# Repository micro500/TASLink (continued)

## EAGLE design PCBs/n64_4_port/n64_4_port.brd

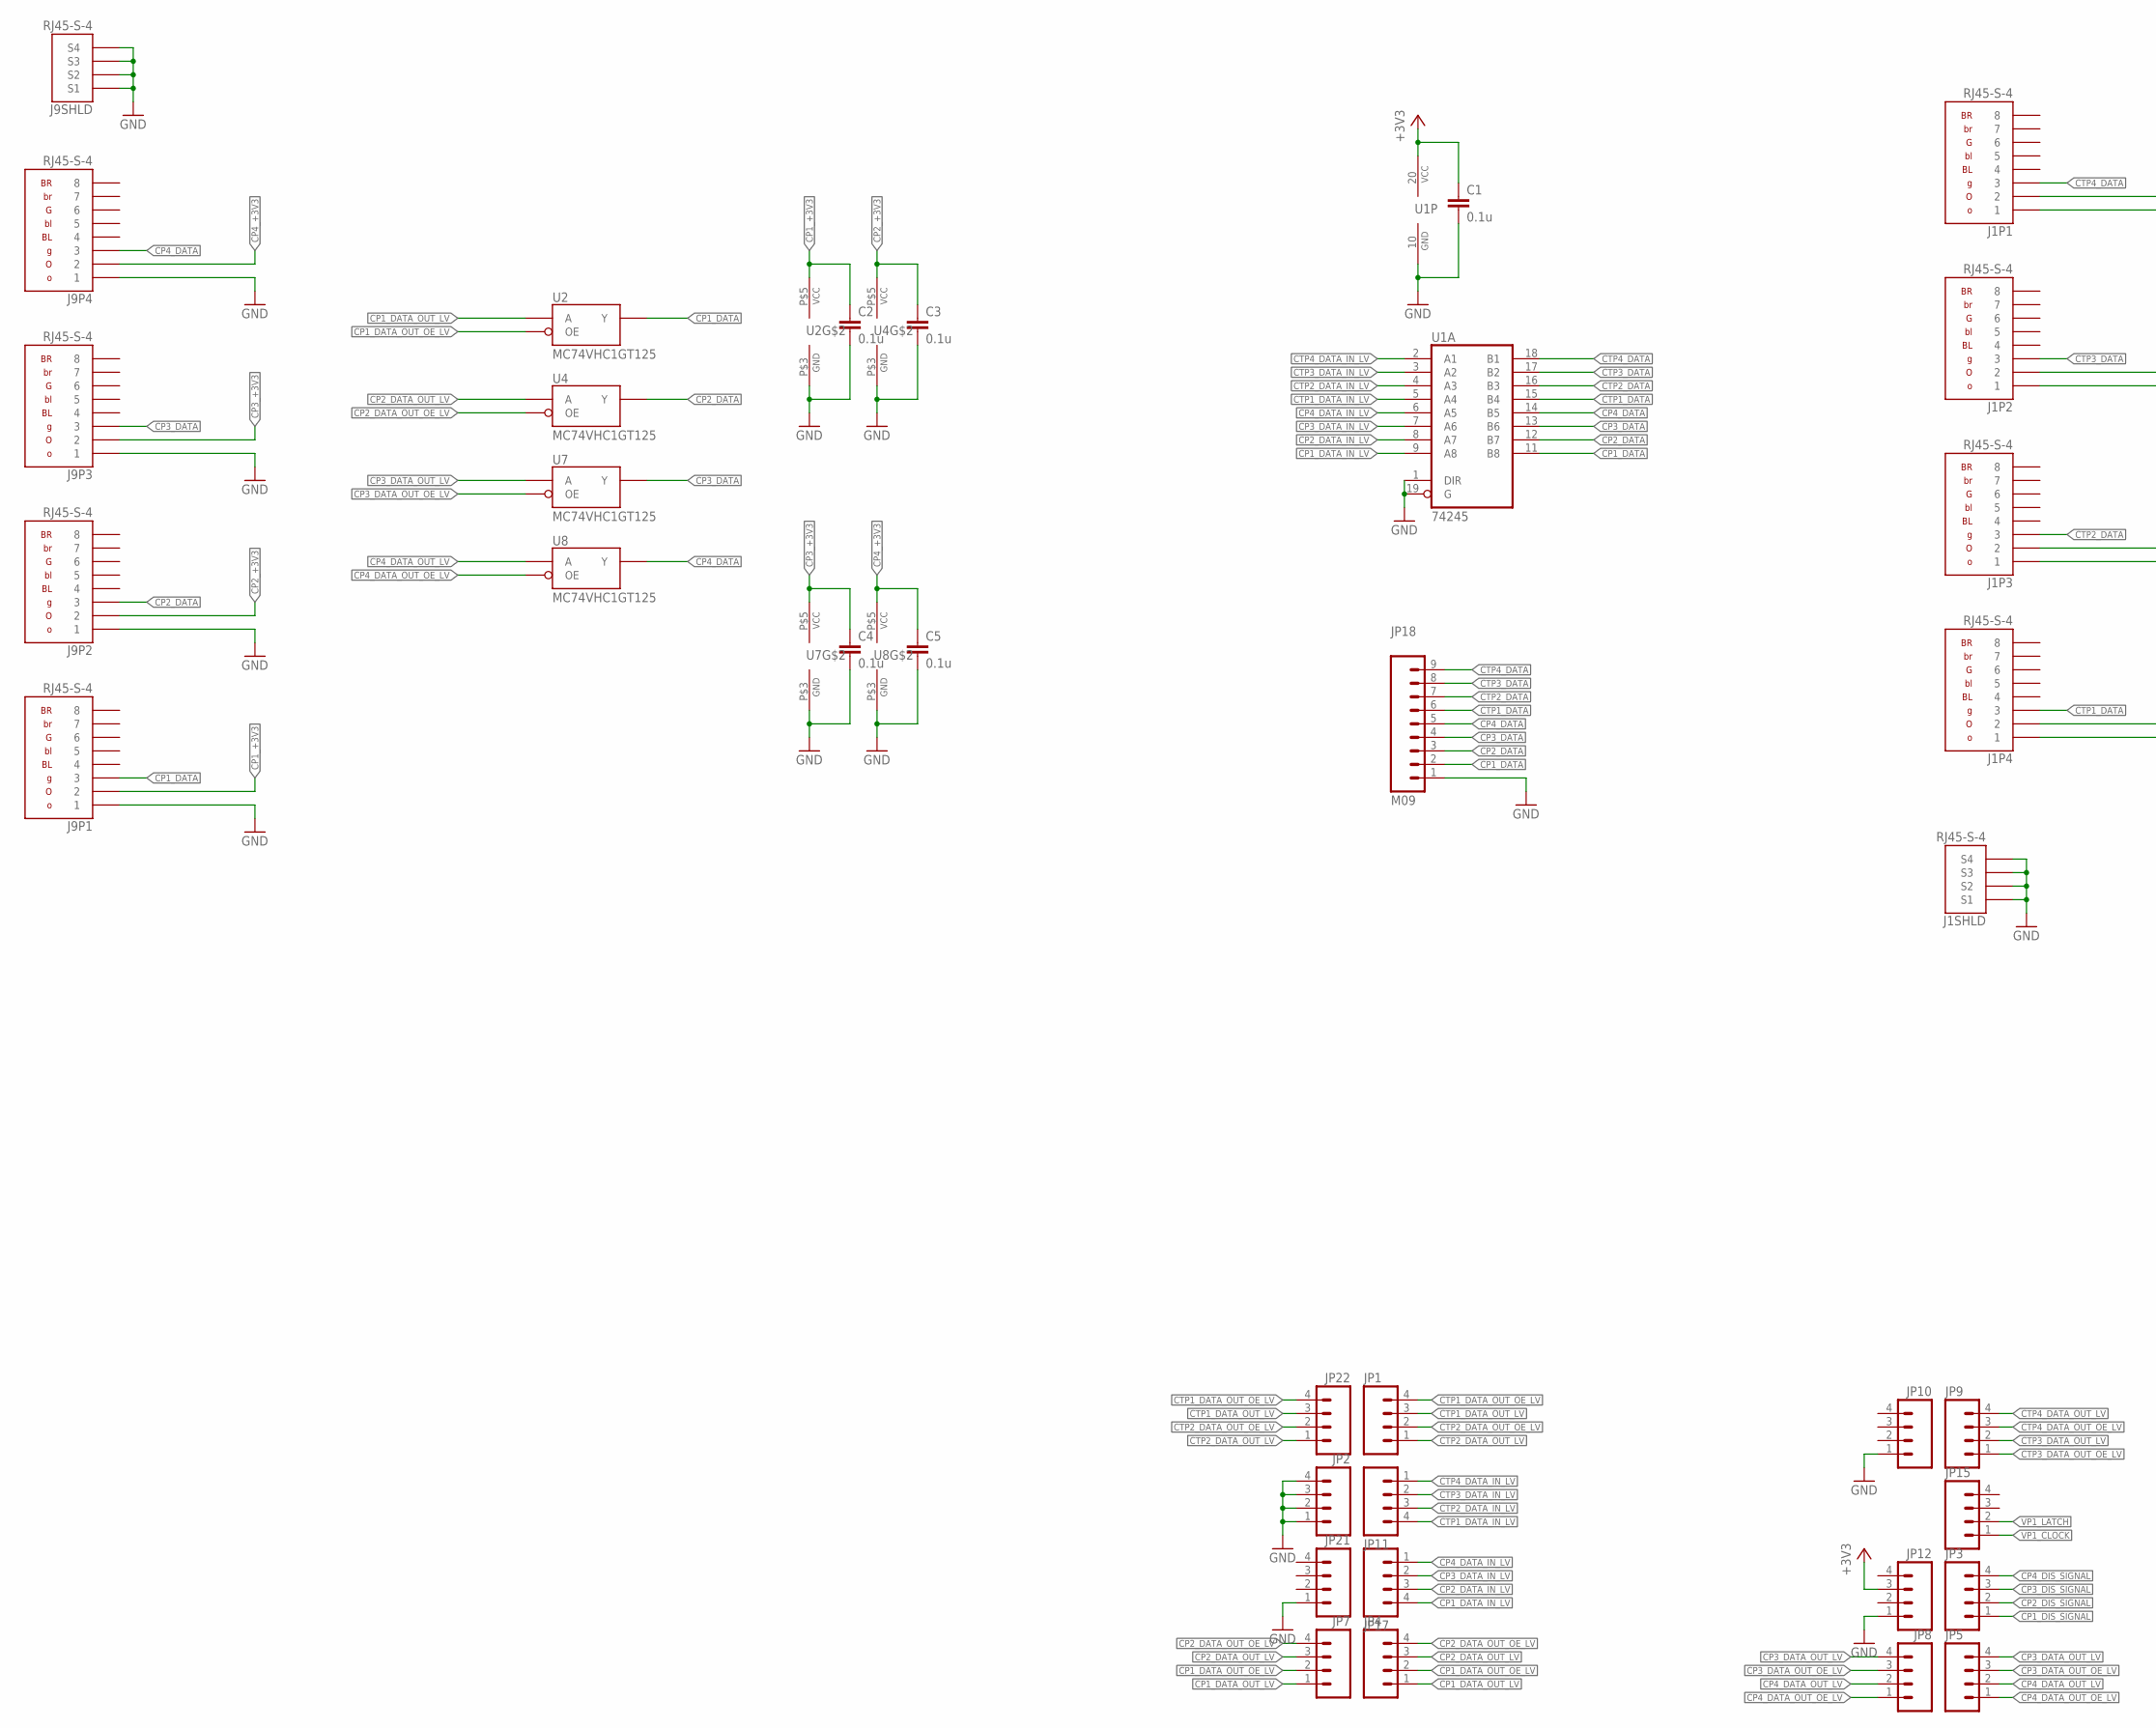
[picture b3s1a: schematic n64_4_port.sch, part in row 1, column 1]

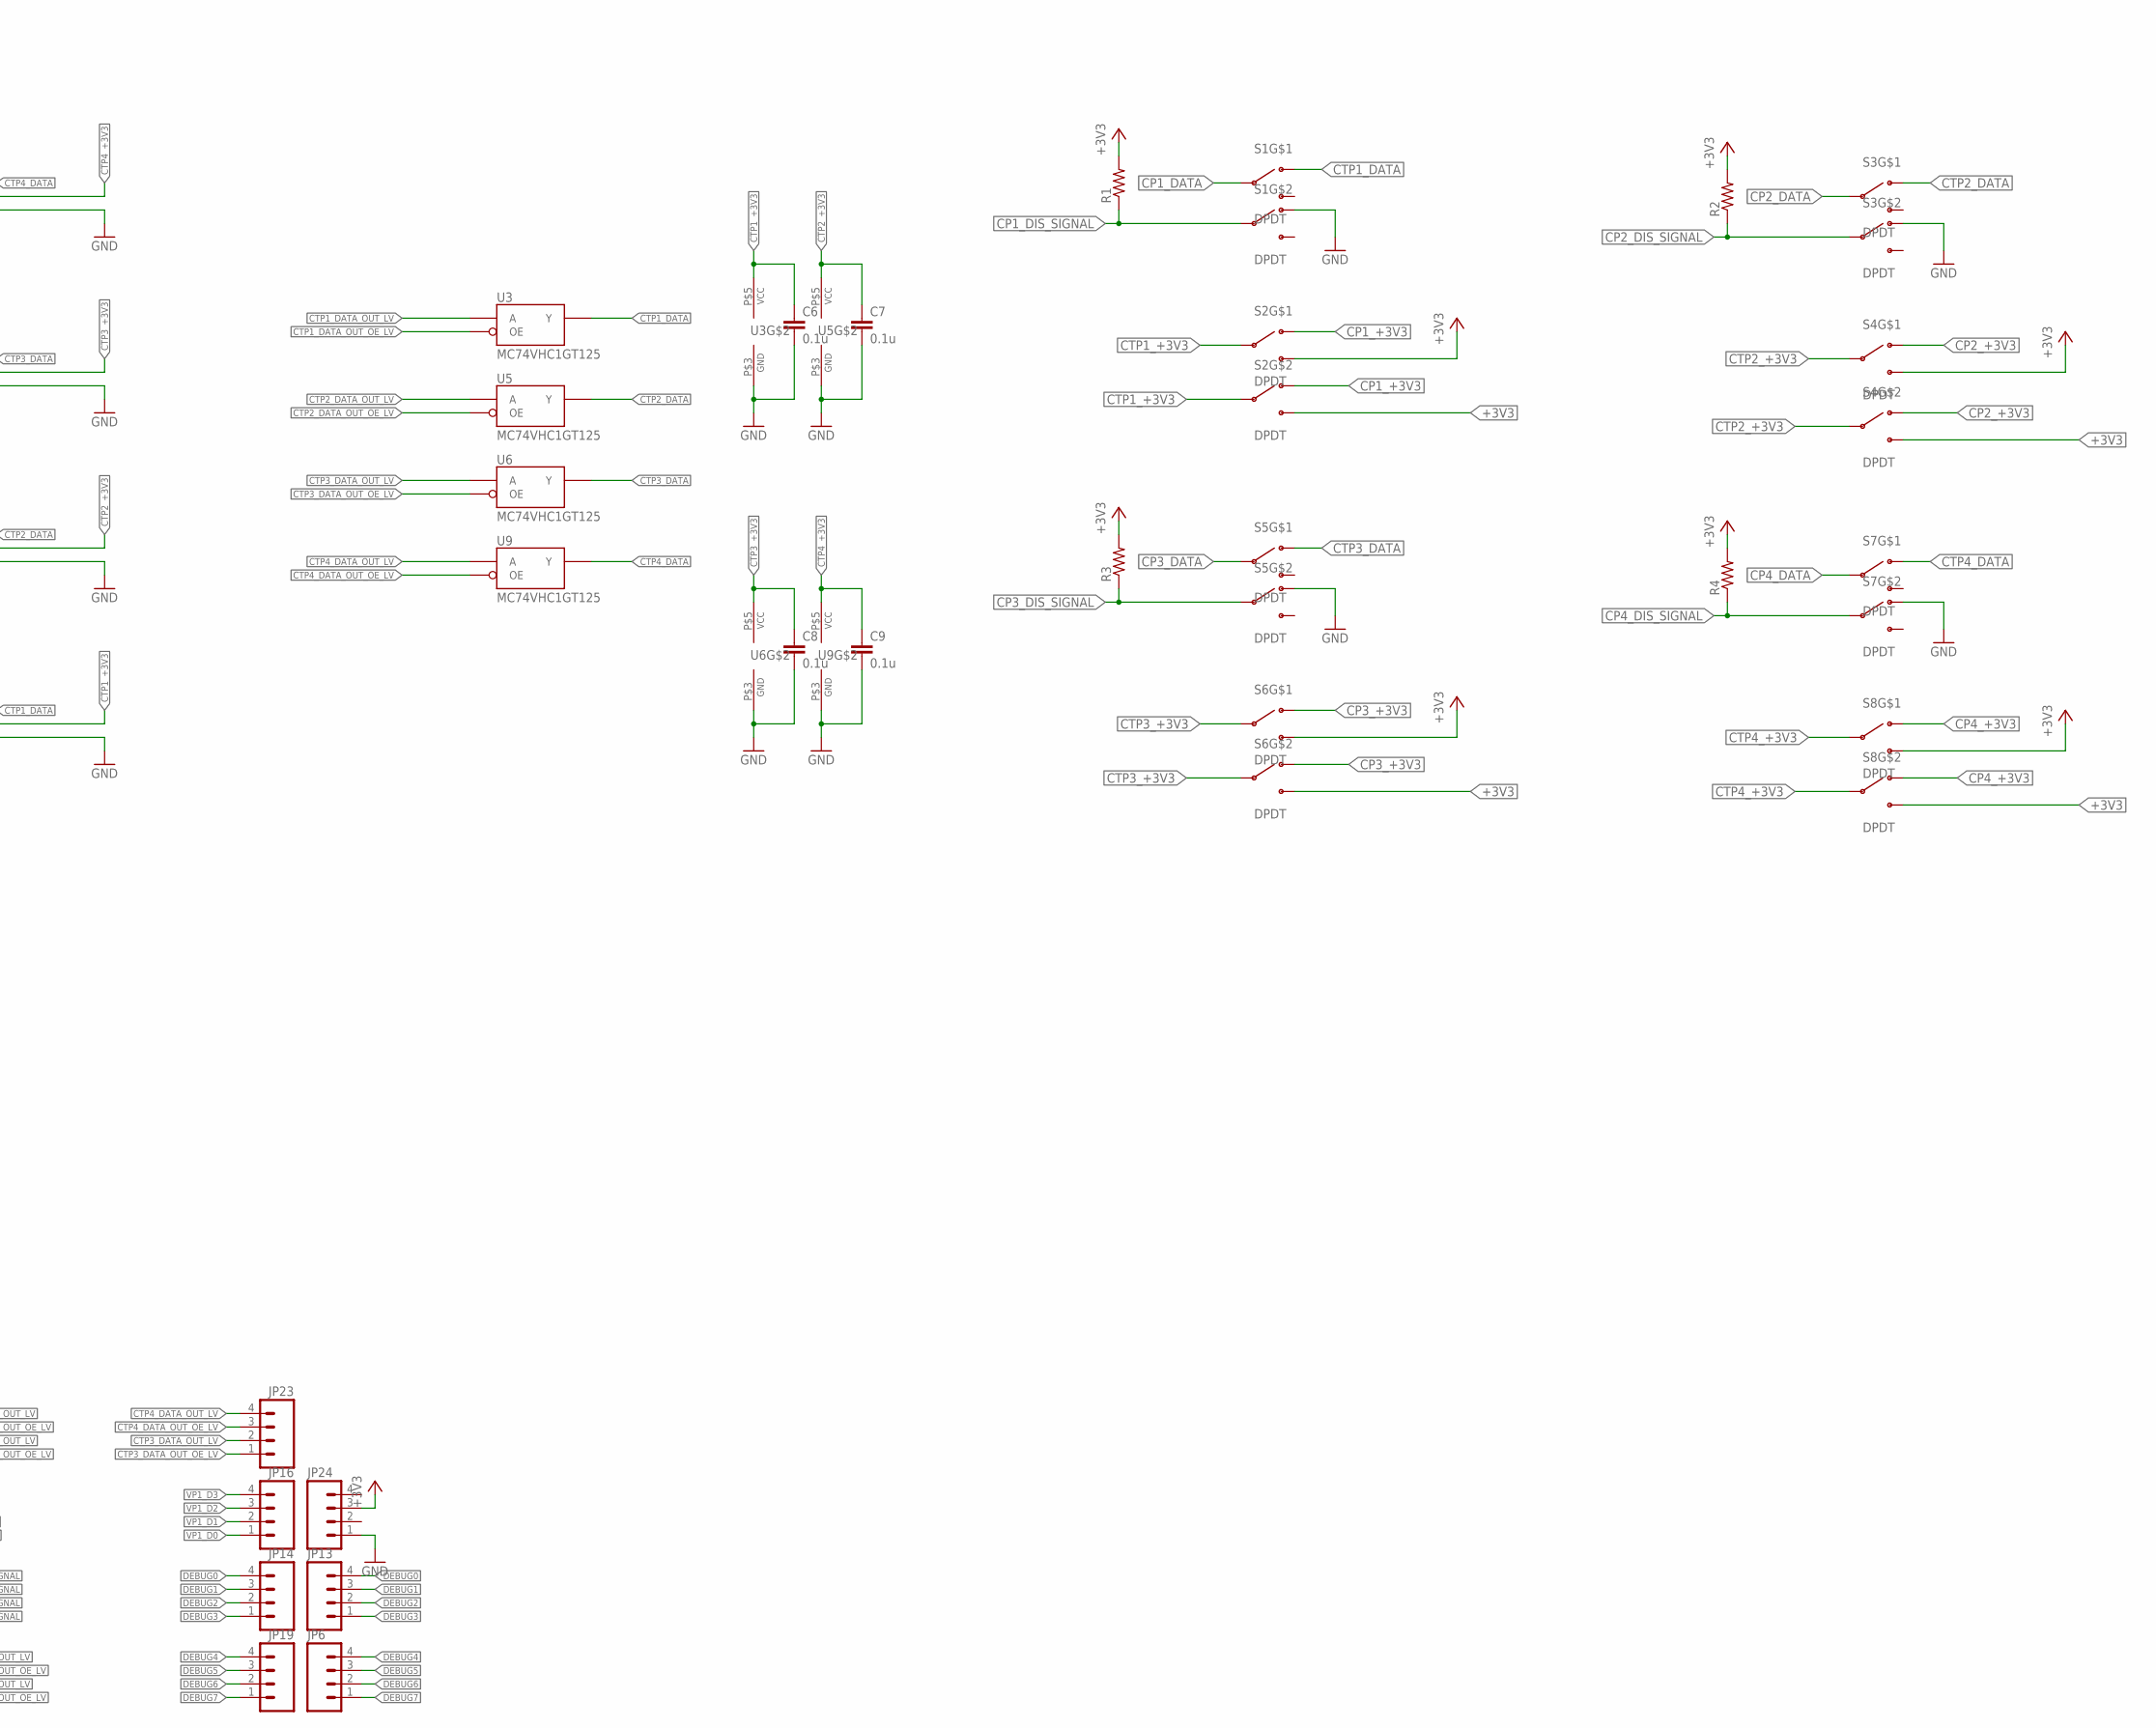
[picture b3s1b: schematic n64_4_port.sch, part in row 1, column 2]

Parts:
C1, C2, C3, C4, C5, C6, C7, C8, C9: 0.1u; C0603
J1, J9: RJ45-S-4
JP1, JP2, JP3, JP4, JP5, JP6, JP7, JP8, JP9, JP10, JP11, JP12, JP13, JP14, JP15, JP16, JP17, JP19, JP21, JP22, JP23, JP24: M04PTH; 1X04
JP18: M09; 1X09
R1, R2, R3, R4: R-US_0207/2V; 0207/2V
S1, S2, S3, S4, S5, S6, S7, S8: DPDT; JS202011CQN
U1: 74245; DIL20
U2, U3, U4, U5, U6, U7, U8, U9: MC74VHC1GT125; TSOP-5

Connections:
+3V3: C1.1, JP12.3, JP24.3, R1.2, R2.2, R3.2, R4.2, S2.3, S2.6 (3), S4.3, S4.6 (3), S6.3, S6.6 (3), S8.3, S8.6 (3), U1.20 (VCC)
CP1_+3V3: C2.1, J9.1-2 (2), S2.1, S2.4 (1), U2.P$5 (VCC)
CP1_DATA: J9.1-3 (3), JP18.2, S1.2, U1.11 (B8), U2.P$4 (Y)
CP1_DATA_IN_LV: JP17.4, U1.9 (A8)
CP1_DATA_OUT_LV: JP4.1, JP7.1, U2.P$2 (A)
CP1_DATA_OUT_OE_LV: JP4.2, JP7.2, U2.P$1 (OE)
CP1_DIS_SIGNAL: JP3.1, R1.1, S1.5 (2)
CP2_+3V3: C3.1, J9.2-2 (2), S4.1, S4.4 (1), U4.P$5 (VCC)
CP2_DATA: J9.2-3 (3), JP18.3, S3.2, U1.12 (B7), U4.P$4 (Y)
CP2_DATA_IN_LV: JP17.3, U1.8 (A7)
CP2_DATA_OUT_LV: JP4.3, JP7.3, U4.P$2 (A)
CP2_DATA_OUT_OE_LV: JP4.4, JP7.4, U4.P$1 (OE)
CP2_DIS_SIGNAL: JP3.2, R2.1, S3.5 (2)
CP3_+3V3: C4.1, J9.3-2 (2), S6.1, S6.4 (1), U7.P$5 (VCC)
CP3_DATA: J9.3-3 (3), JP18.4, S5.2, U1.13 (B6), U7.P$4 (Y)
CP3_DATA_IN_LV: JP17.2, U1.7 (A6)
CP3_DATA_OUT_LV: JP5.4, JP8.4, U7.P$2 (A)
CP3_DATA_OUT_OE_LV: JP5.3, JP8.3, U7.P$1 (OE)
CP3_DIS_SIGNAL: JP3.3, R3.1, S5.5 (2)
CP4_+3V3: C5.1, J9.4-2 (2), S8.1, S8.4 (1), U8.P$5 (VCC)
CP4_DATA: J9.4-3 (3), JP18.5, S7.2, U1.14 (B5), U8.P$4 (Y)
CP4_DATA_IN_LV: JP17.1, U1.6 (A5)
CP4_DATA_OUT_LV: JP5.2, JP8.2, U8.P$2 (A)
CP4_DATA_OUT_OE_LV: JP5.1, JP8.1, U8.P$1 (OE)
CP4_DIS_SIGNAL: JP3.4, R4.1, S7.5 (2)
CTP1_+3V3: C6.1, J1.4-2 (2), S2.2, S2.5 (2), U3.P$5 (VCC)
CTP1_DATA: J1.4-3 (3), JP18.6, S1.1, U1.15 (B4), U3.P$4 (Y)
CTP1_DATA_IN_LV: JP11.4, U1.5 (A4)
CTP1_DATA_OUT_LV: JP1.3, JP22.3, U3.P$2 (A)
CTP1_DATA_OUT_OE_LV: JP1.4, JP22.4, U3.P$1 (OE)
CTP2_+3V3: C7.1, J1.3-2 (2), S4.2, S4.5 (2), U5.P$5 (VCC)
CTP2_DATA: J1.3-3 (3), JP18.7, S3.1, U1.16 (B3), U5.P$4 (Y)
CTP2_DATA_IN_LV: JP11.3, U1.4 (A3)
CTP2_DATA_OUT_LV: JP1.1, JP22.1, U5.P$2 (A)
CTP2_DATA_OUT_OE_LV: JP1.2, JP22.2, U5.P$1 (OE)
CTP3_+3V3: C8.1, J1.2-2 (2), S6.2, S6.5 (2), U6.P$5 (VCC)
CTP3_DATA: J1.2-3 (3), JP18.8, S5.1, U1.17 (B2), U6.P$4 (Y)
CTP3_DATA_IN_LV: JP11.2, U1.3 (A2)
CTP3_DATA_OUT_LV: JP9.2, JP23.2, U6.P$2 (A)
CTP3_DATA_OUT_OE_LV: JP9.1, JP23.1, U6.P$1 (OE)
CTP4_+3V3: C9.1, J1.1-2 (2), S8.2, S8.5 (2), U9.P$5 (VCC)
CTP4_DATA: J1.1-3 (3), JP18.9, S7.1, U1.18 (B1), U9.P$4 (Y)
CTP4_DATA_IN_LV: JP11.1, U1.2 (A1)
CTP4_DATA_OUT_LV: JP9.4, JP23.4, U9.P$2 (A)
CTP4_DATA_OUT_OE_LV: JP9.3, JP23.3, U9.P$1 (OE)
DEBUG0: JP13.4, JP14.4
DEBUG1: JP13.3, JP14.3
DEBUG2: JP13.2, JP14.2
DEBUG3: JP13.1, JP14.1
DEBUG4: JP6.4, JP19.4
DEBUG5: JP6.3, JP19.3
DEBUG6: JP6.2, JP19.2
DEBUG7: JP6.1, JP19.1
GND: C1.2, C2.2, C3.2, C4.2, C5.2, C6.2, C7.2, C8.2, C9.2, J1.1-1 (1), J1.2-1 (1), J1.3-1 (1), J1.4-1 (1), J1.S1, J1.S2, J1.S3, J1.S4, J9.1-1 (1), J9.2-1 (1), J9.3-1 (1), J9.4-1 (1), J9.S1, J9.S2, J9.S3, J9.S4, JP2.1, JP2.2, JP2.3, JP2.4, JP10.1, JP12.1, JP18.1, JP21.1, JP24.1, S1.4 (1), S3.4 (1), S5.4 (1), S7.4 (1), U1.1 (DIR), U1.10 (GND), U1.19 (G), U2.P$3 (GND), U3.P$3 (GND), U4.P$3 (GND), U5.P$3 (GND), U6.P$3 (GND), U7.P$3 (GND), U8.P$3 (GND), U9.P$3 (GND)
VP1_CLOCK: JP15.1
VP1_D0: JP16.1
VP1_D1: JP16.2
VP1_D2: JP16.3
VP1_D3: JP16.4
VP1_LATCH: JP15.2

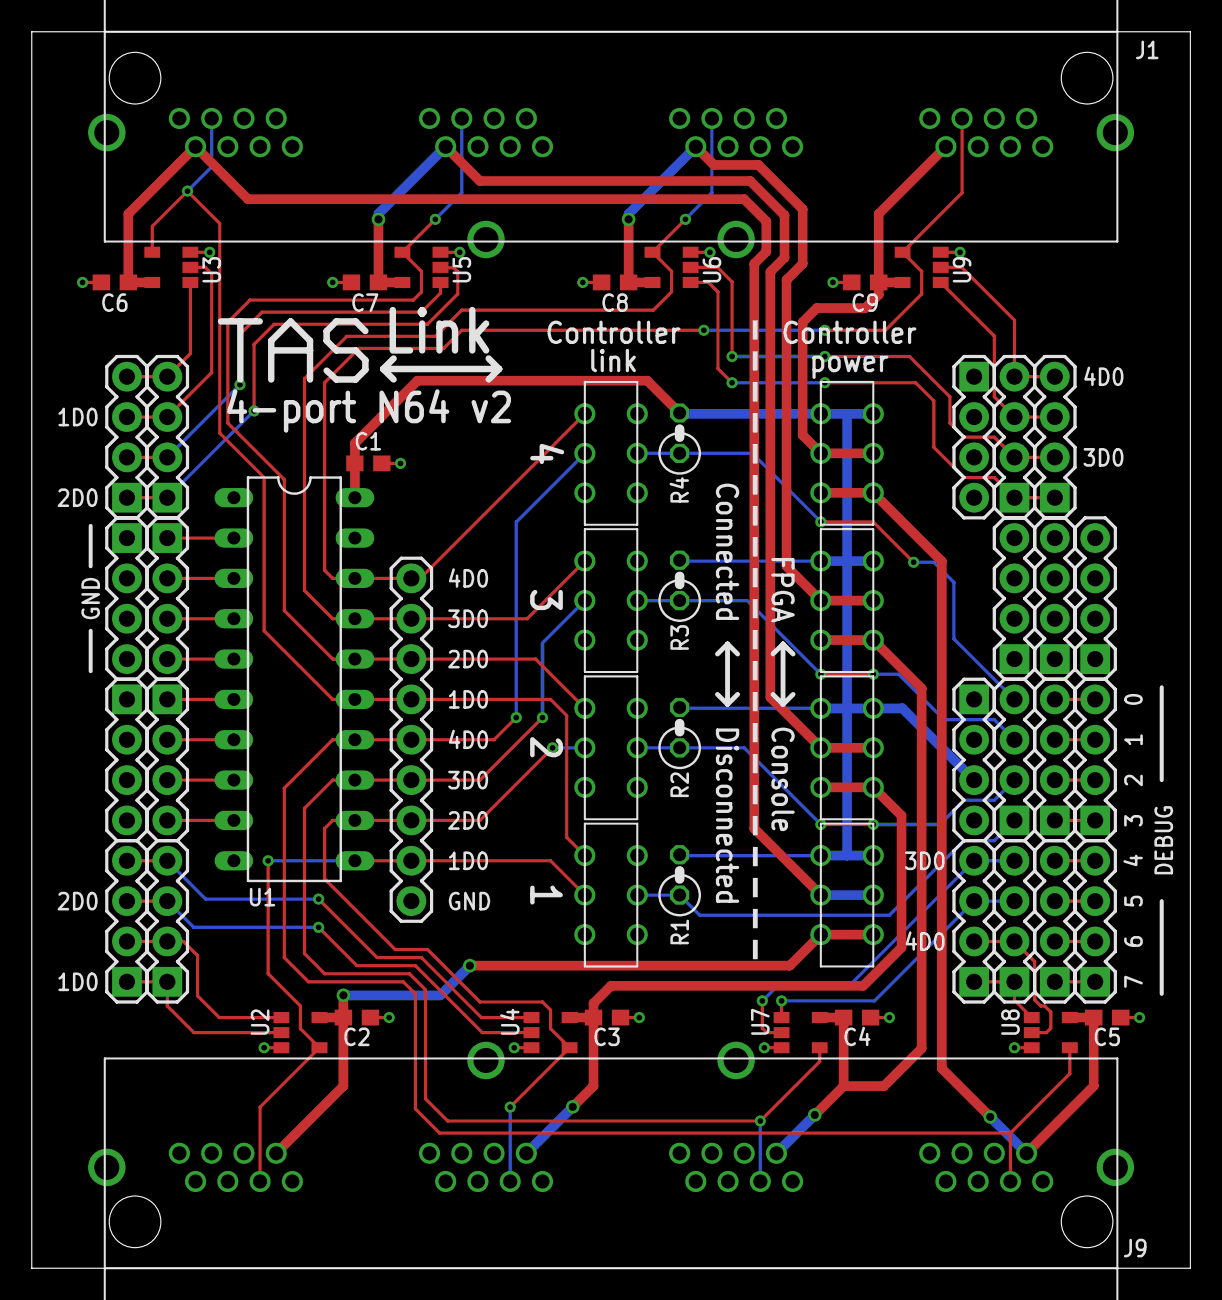
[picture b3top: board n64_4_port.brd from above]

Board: 2 copper layers, 72.9 x 77.9 mm, 55 parts (0 on the bottom side), 54 nets.

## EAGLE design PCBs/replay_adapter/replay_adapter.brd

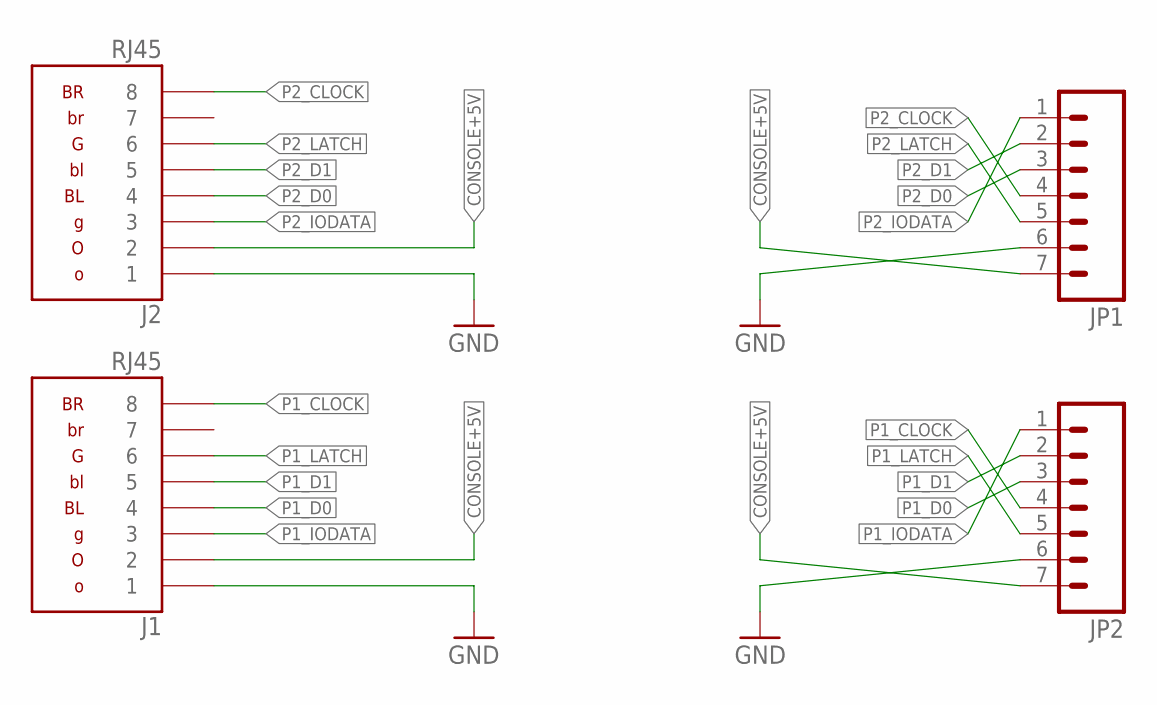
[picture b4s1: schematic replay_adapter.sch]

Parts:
J1, J2: RJ45
JP1, JP2: M07; 1X07

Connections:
CONSOLE+5V: J1.2, J2.2, JP1.7, JP2.7
GND: J1.1, J2.1, JP1.6, JP2.6
P1_CLOCK: J1.8, JP2.4
P1_D0: J1.4, JP2.3
P1_D1: J1.5, JP2.2
P1_IODATA: J1.3, JP2.1
P1_LATCH: J1.6, JP2.5
P2_CLOCK: J2.8, JP1.4
P2_D0: J2.4, JP1.3
P2_D1: J2.5, JP1.2
P2_IODATA: J2.3, JP1.1
P2_LATCH: J2.6, JP1.5

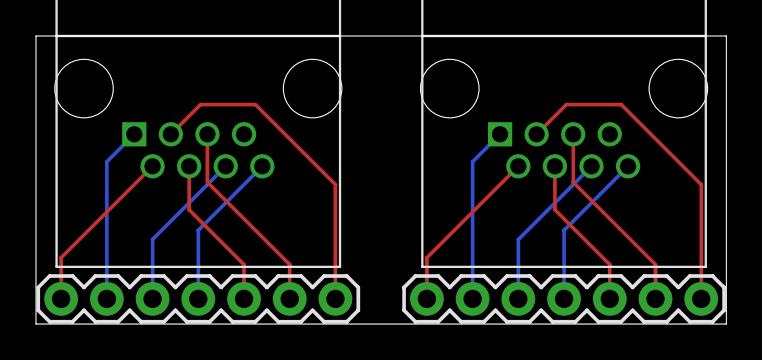
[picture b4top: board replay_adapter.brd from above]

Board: 2 copper layers, 38.4 x 16.0 mm, 4 parts (0 on the bottom side), 12 nets.

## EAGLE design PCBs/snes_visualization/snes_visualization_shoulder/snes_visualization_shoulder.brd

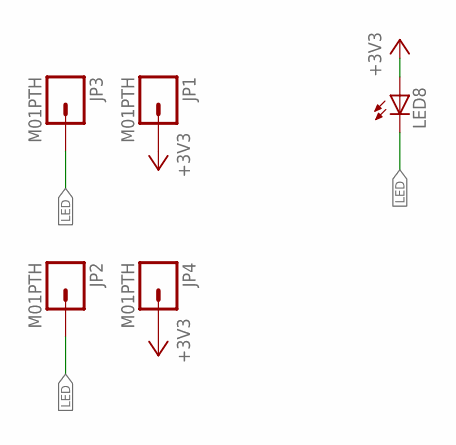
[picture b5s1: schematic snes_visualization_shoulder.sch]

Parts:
JP1, JP2, JP3, JP4: M01PTH; 1X01
LED8: LED5MM

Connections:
+3V3: JP1.1, JP4.1, LED8.A
LED: JP2.1, JP3.1, LED8.K (C)

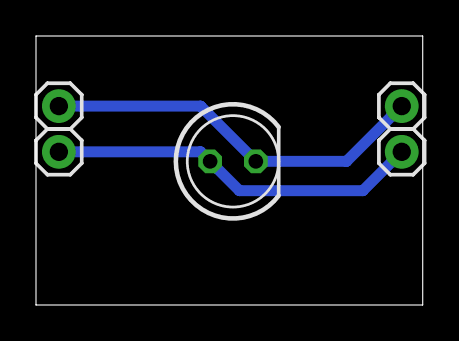
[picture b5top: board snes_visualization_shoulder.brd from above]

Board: 2 copper layers, 21.5 x 14.9 mm, 5 parts (0 on the bottom side), 2 nets.

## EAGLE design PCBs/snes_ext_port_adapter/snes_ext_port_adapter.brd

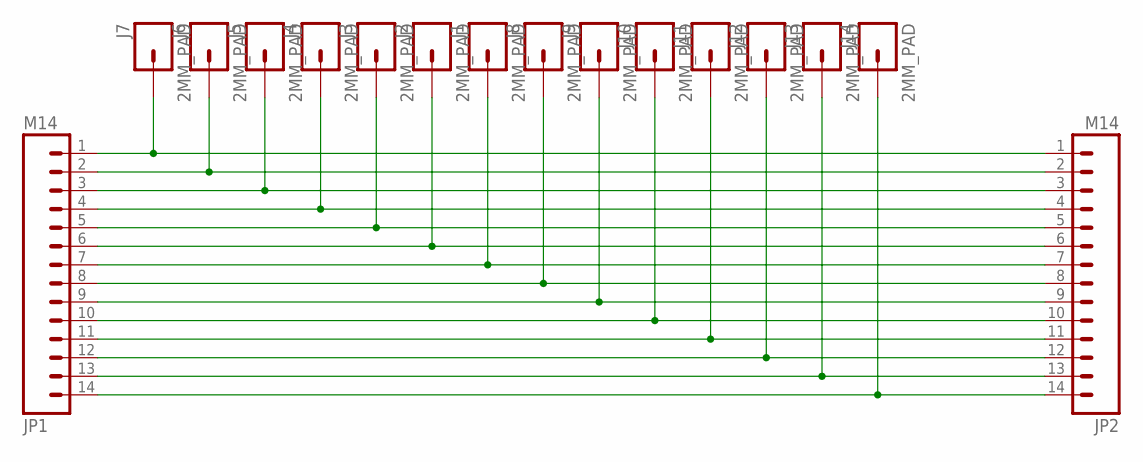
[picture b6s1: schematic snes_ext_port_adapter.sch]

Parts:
J1, J2, J3, J4, J5, J6, J7, J8, J9, J10, J11, J12, J13, J14: 2MM_PAD; 1MM_PAD
JP1, JP2: M14; 1X14

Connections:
unnamed: J7.P$1, JP1.1, JP2.1
unnamed: J6.P$1, JP1.2, JP2.2
unnamed: J5.P$1, JP1.3, JP2.3
unnamed: J4.P$1, JP1.4, JP2.4
unnamed: J3.P$1, JP1.5, JP2.5
unnamed: J2.P$1, JP1.6, JP2.6
unnamed: J1.P$1, JP1.7, JP2.7
unnamed: J8.P$1, JP1.8, JP2.8
unnamed: J9.P$1, JP1.9, JP2.9
unnamed: J10.P$1, JP1.10, JP2.10
unnamed: J11.P$1, JP1.11, JP2.11
unnamed: J12.P$1, JP1.12, JP2.12
unnamed: J13.P$1, JP1.13, JP2.13
unnamed: J14.P$1, JP1.14, JP2.14

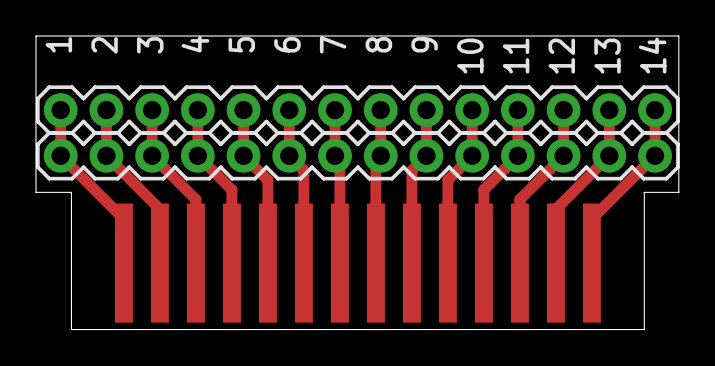
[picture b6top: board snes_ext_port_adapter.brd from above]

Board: 2 copper layers, 35.7 x 16.3 mm, 16 parts (0 on the bottom side), 14 nets.

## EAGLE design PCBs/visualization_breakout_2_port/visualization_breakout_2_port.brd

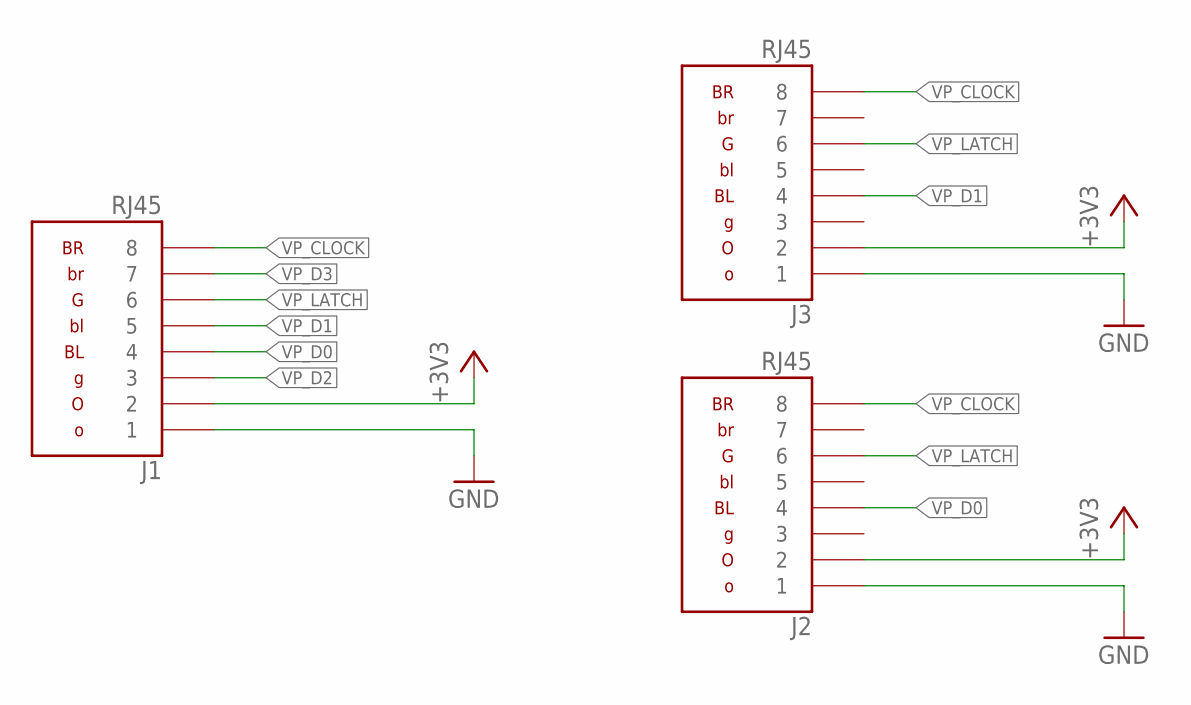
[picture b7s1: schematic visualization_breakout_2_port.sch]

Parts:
J1, J2, J3: RJ45

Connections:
+3V3: J1.2, J2.2, J3.2
GND: J1.1, J2.1, J3.1
VP_CLOCK: J1.8, J2.8, J3.8
VP_D0: J1.4, J2.4
VP_D1: J1.5, J3.4
VP_D2: J1.3
VP_D3: J1.7
VP_LATCH: J1.6, J2.6, J3.6

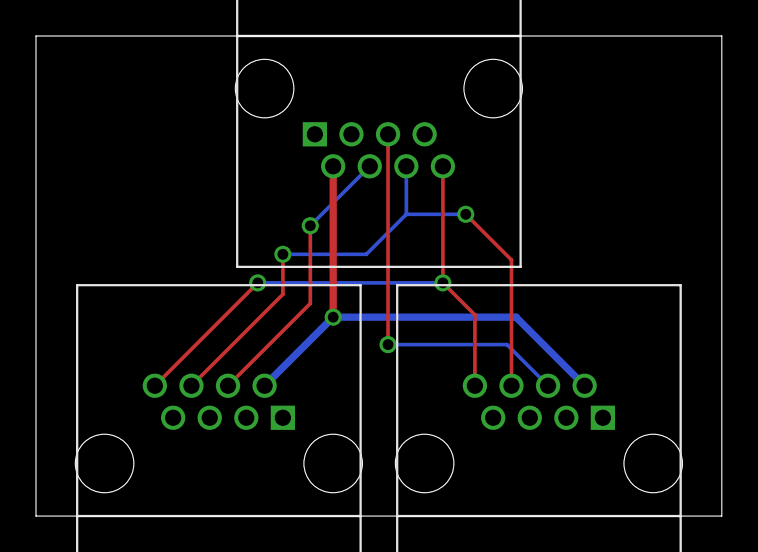
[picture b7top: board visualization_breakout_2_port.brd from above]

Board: 2 copper layers, 38.1 x 26.7 mm, 3 parts (0 on the bottom side), 6 nets.

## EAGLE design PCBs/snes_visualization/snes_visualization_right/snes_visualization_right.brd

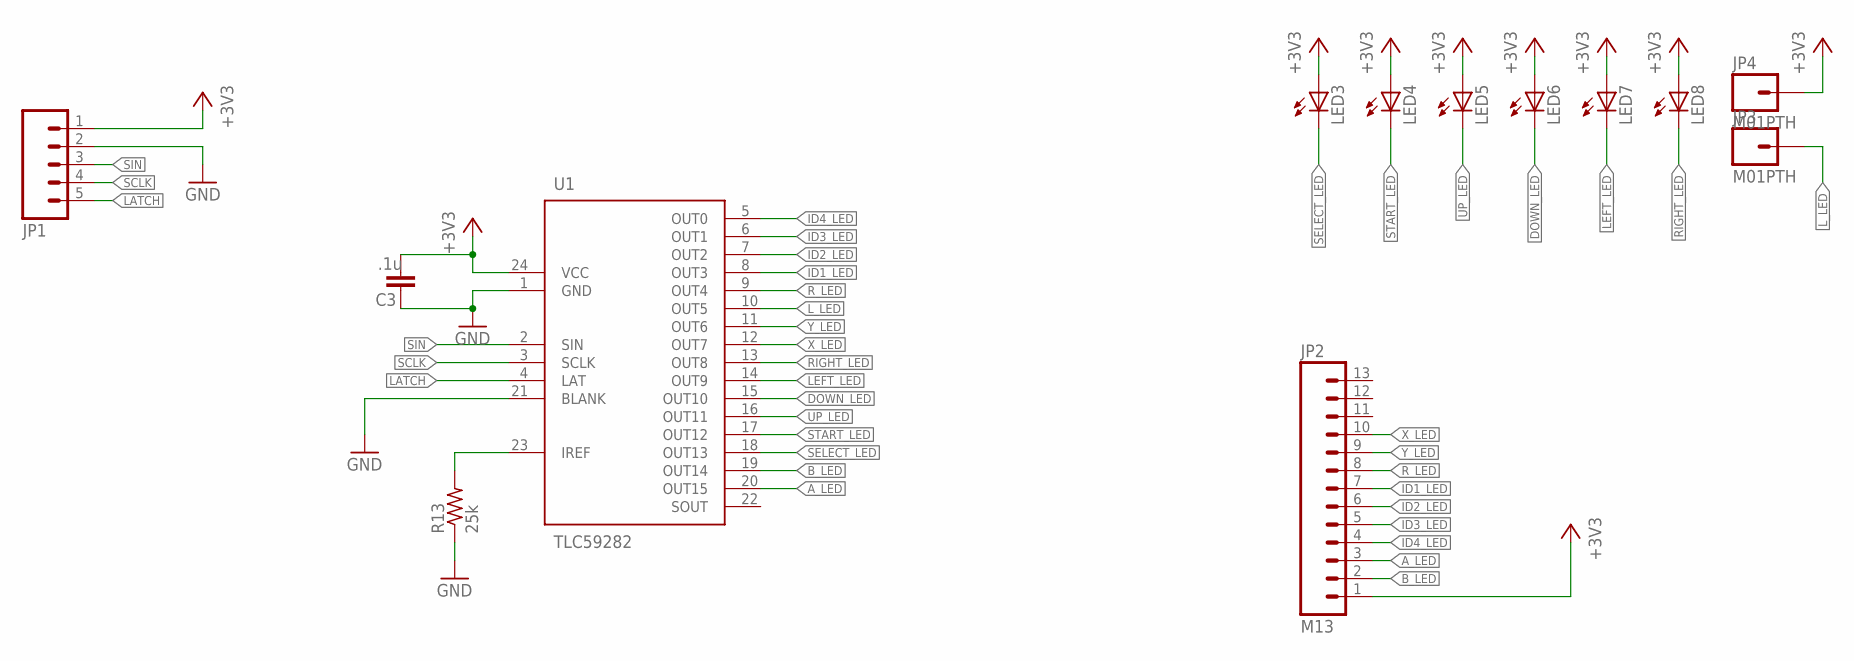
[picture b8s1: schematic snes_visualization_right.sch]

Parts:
C3: .1u; C0603; MOUSER# 80-C0603C104K5R
JP1: M05PTH; 1X05
JP2: M13; 1X13
JP3, JP4: M01PTH; 1X01
LED3, LED4: LED3MM
LED5, LED6, LED7, LED8: LED5MM
R13: 25k; R0805
U1: TLC59282; R-PDSO-G24

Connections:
+3V3: C3.1, JP1.1, JP2.1, JP4.1, LED3.A, LED4.A, LED5.A, LED6.A, LED7.A, LED8.A, U1.24 (VCC)
A_LED: JP2.3, U1.20 (OUT15)
B_LED: JP2.2, U1.19 (OUT14)
DOWN_LED: LED6.K (C), U1.15 (OUT10)
GND: C3.2, JP1.2, R13.1, U1.1 (GND), U1.21 (BLANK)
ID1_LED: JP2.7, U1.8 (OUT3)
ID2_LED: JP2.6, U1.7 (OUT2)
ID3_LED: JP2.5, U1.6 (OUT1)
ID4_LED: JP2.4, U1.5 (OUT0)
LATCH: JP1.5, U1.4 (LAT)
LEFT_LED: LED7.K (C), U1.14 (OUT9)
L_LED: JP3.1, U1.10 (OUT5)
unnamed: R13.2, U1.23 (IREF)
RIGHT_LED: LED8.K (C), U1.13 (OUT8)
R_LED: JP2.8, U1.9 (OUT4)
SCLK: JP1.4, U1.3 (SCLK)
SELECT_LED: LED3.K (C), U1.18 (OUT13)
SIN: JP1.3, U1.2 (SIN)
START_LED: LED4.K (C), U1.17 (OUT12)
UP_LED: LED5.K (C), U1.16 (OUT11)
X_LED: JP2.10, U1.12 (OUT7)
Y_LED: JP2.9, U1.11 (OUT6)

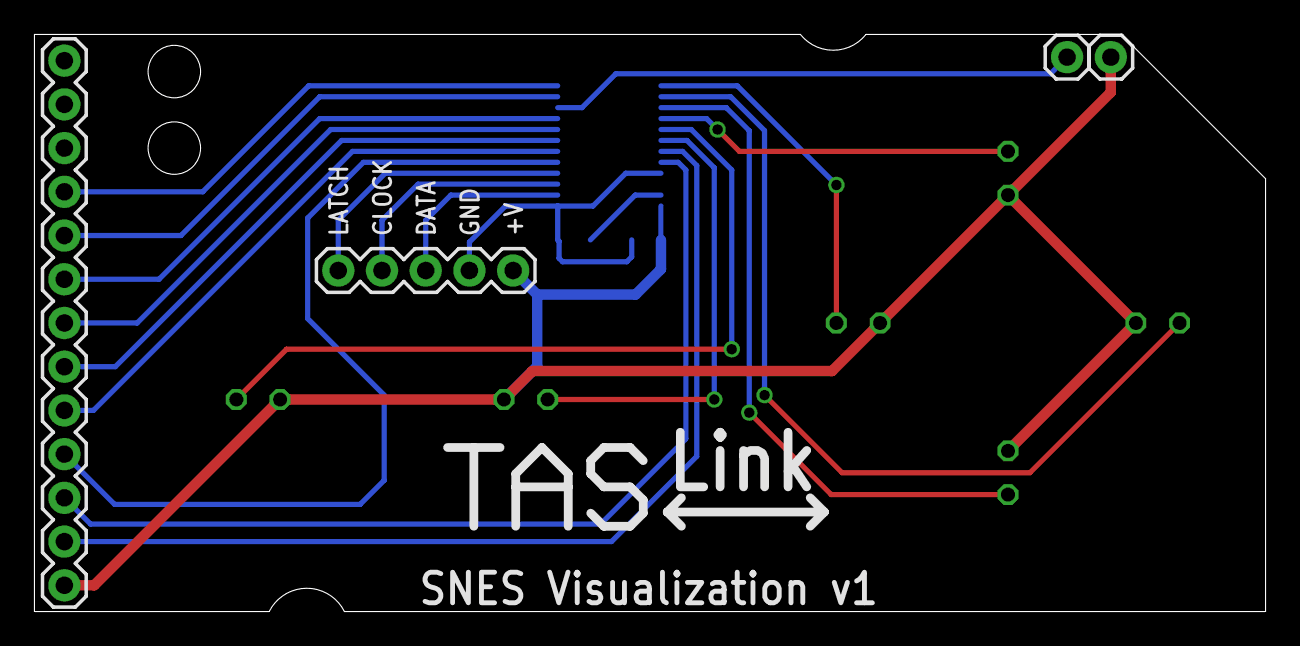
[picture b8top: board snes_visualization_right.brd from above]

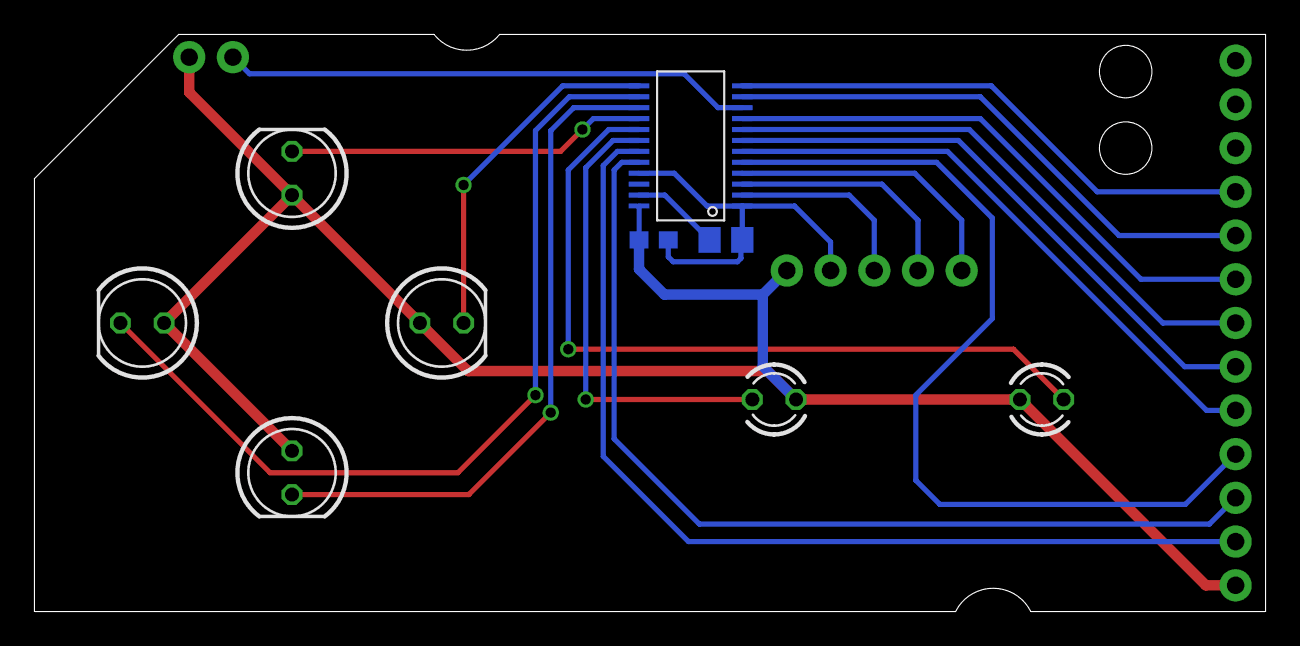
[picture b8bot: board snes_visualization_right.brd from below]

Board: 2 copper layers, 71.5 x 33.5 mm, 13 parts (9 on the bottom side), 22 nets.
